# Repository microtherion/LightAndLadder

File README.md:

[KiCad](http://kicad-pcb.org) design of simple testbench for microcontrollers.

The resistor networks should be pairwise identical; I've used 680Ω for the LED resistors, with 
blue & green LEDs (note that the LEDs are connected to the closest pin, so top and bottom row are 
each connected to **both** resistor networks), and 1kΩ for the ladder resistors. 

So what is the "ladder" part good for? It's the world's most primitive analog computer, 
a.k.a a voltage divider that can be used to generate a wide 
range of fractions of VCC, according to the formula printed on the board:

To generate a particular voltage, connect your analog input pin to one or several of the pins 
in the top row (next to the `+`) and one or several in the bottom row (next to `-`).

If VCC (applied to the `+` pin) is 5V, then

* `+1` / `-1` will generate `5V * (1 / (1+1)) = 2.5V` (as will `+2` / `-2` or `+4` / `-4`).
* `+1` / `-2` will generate `5V * (1 / (1+2)) = 1.6V`.
* `+2` / `-1` will generate `5V * (2 / (2+1)) = 3.2V`.
* `+1` / `-1,-2` will generate `5V * (1 / 1+1+2) = 1.25V`.

PCB available at [OSH Park](https://oshpark.com/projects/oy5yst8f)

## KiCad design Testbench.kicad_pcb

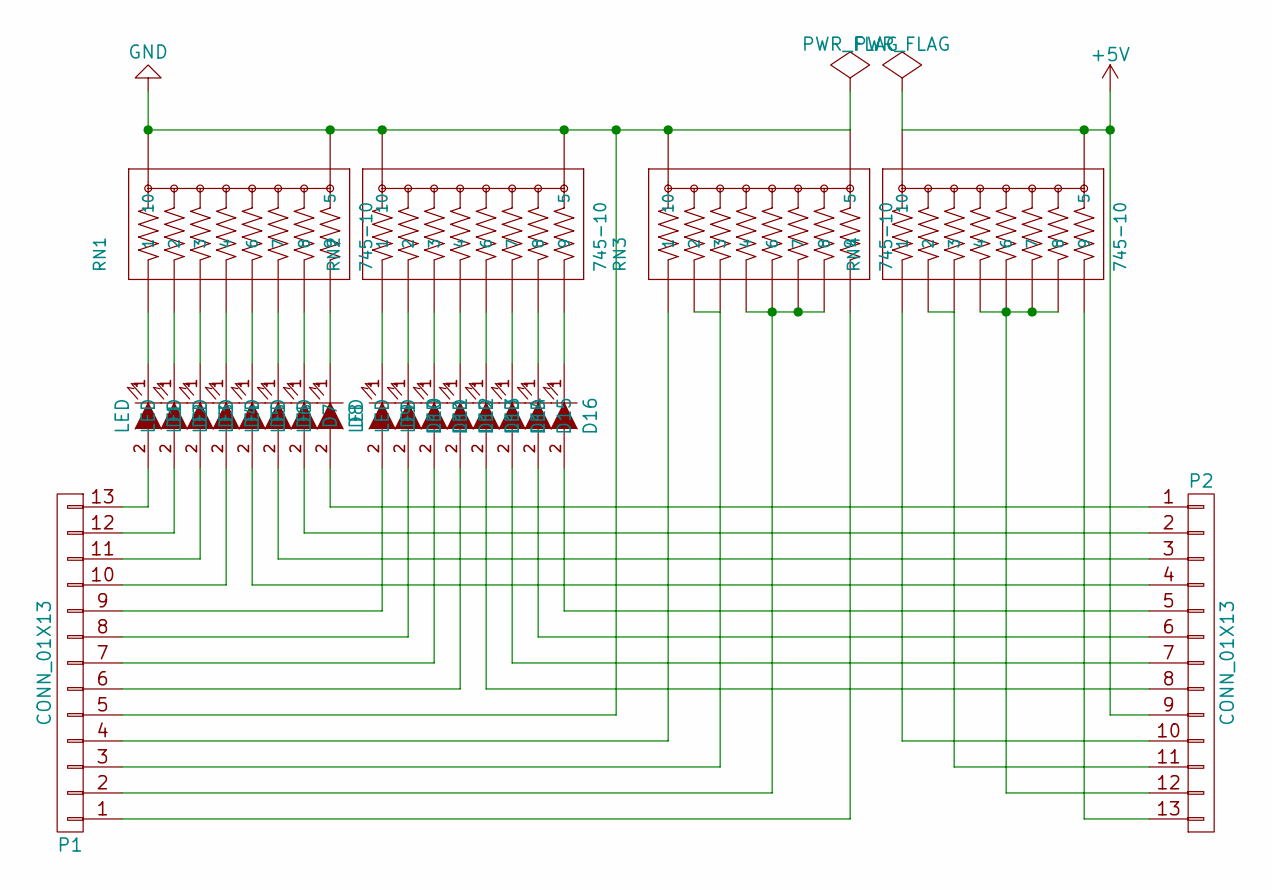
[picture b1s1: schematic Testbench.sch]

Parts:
D1, D2, D3, D4, D5, D6, D7, D8, D9, D10, D11, D12, D13, D14, D15, D16: LED; LED-1206
P1, P2: CONN_01X13; Socket_Strip_Straight_1x13
RN1, RN2, RN3, RN4: 745-10; resistor-array-745-10

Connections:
+5V: P2.9, RN4.5, RN4.10
GND: P1.5, RN1.5, RN1.10, RN2.5, RN2.10, RN3.5, RN3.10
unnamed: D1.1 (K), RN1.1
unnamed: D1.2 (A), P1.13
unnamed: D2.1 (K), RN1.2
unnamed: D2.2 (A), P1.12
unnamed: D3.1 (K), RN1.3
unnamed: D3.2 (A), P1.11
unnamed: D4.1 (K), RN1.4
unnamed: D4.2 (A), P1.10
unnamed: D5.1 (K), RN1.6
unnamed: D5.2 (A), P2.4
unnamed: D6.1 (K), RN1.7
unnamed: D6.2 (A), P2.3
unnamed: D7.1 (K), RN1.8
unnamed: D7.2 (A), P2.2
unnamed: D8.1 (K), RN1.9
unnamed: D8.2 (A), P2.1
unnamed: D9.1 (K), RN2.1
unnamed: D9.2 (A), P1.9
unnamed: D10.1 (K), RN2.2
unnamed: D10.2 (A), P1.8
unnamed: D11.1 (K), RN2.3
unnamed: D11.2 (A), P1.7
unnamed: D12.1 (K), RN2.4
unnamed: D12.2 (A), P1.6
unnamed: D13.1 (K), RN2.6
unnamed: D13.2 (A), P2.8
unnamed: D14.1 (K), RN2.7
unnamed: D14.2 (A), P2.7
unnamed: D15.1 (K), RN2.8
unnamed: D15.2 (A), P2.6
unnamed: D16.1 (K), RN2.9
unnamed: D16.2 (A), P2.5
unnamed: P1.1, RN3.9
unnamed: P1.2, RN3.4, RN3.6, RN3.7, RN3.8
unnamed: P1.3, RN3.2, RN3.3
unnamed: P1.4, RN3.1
unnamed: P2.10, RN4.1
unnamed: P2.11, RN4.2, RN4.3
unnamed: P2.12, RN4.4, RN4.6, RN4.7, RN4.8
unnamed: P2.13, RN4.9

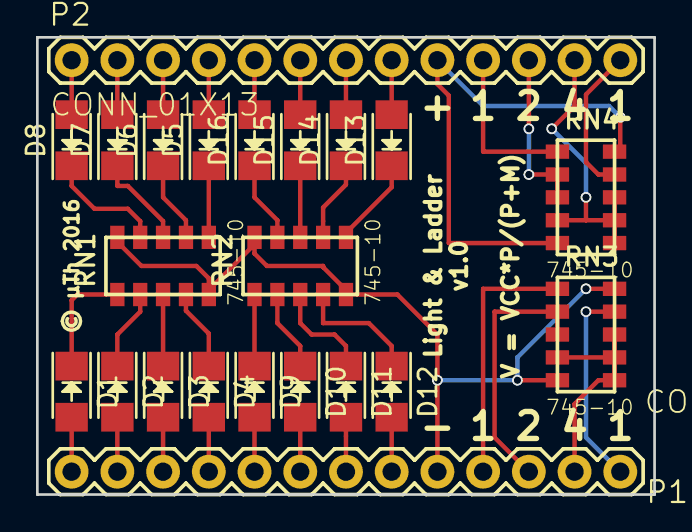
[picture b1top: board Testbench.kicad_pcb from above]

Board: 2 copper layers, 34.3 x 25.4 mm, 22 parts (0 on the bottom side), 42 nets.

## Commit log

2016-05-25 Light & Ladder v1.0
2016-06-25 Add graphics
2016-06-25 Created README
